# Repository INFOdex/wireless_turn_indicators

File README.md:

# Testing of Wireless Turn Indicators for Automotive Applications
Created as a capstone project for Robert S. and Peter L.

This project was mostly done as a proof-of-concept, but was eventually completed as a capstone project. 

The final copy of the code was stored on the university's private GIT server.

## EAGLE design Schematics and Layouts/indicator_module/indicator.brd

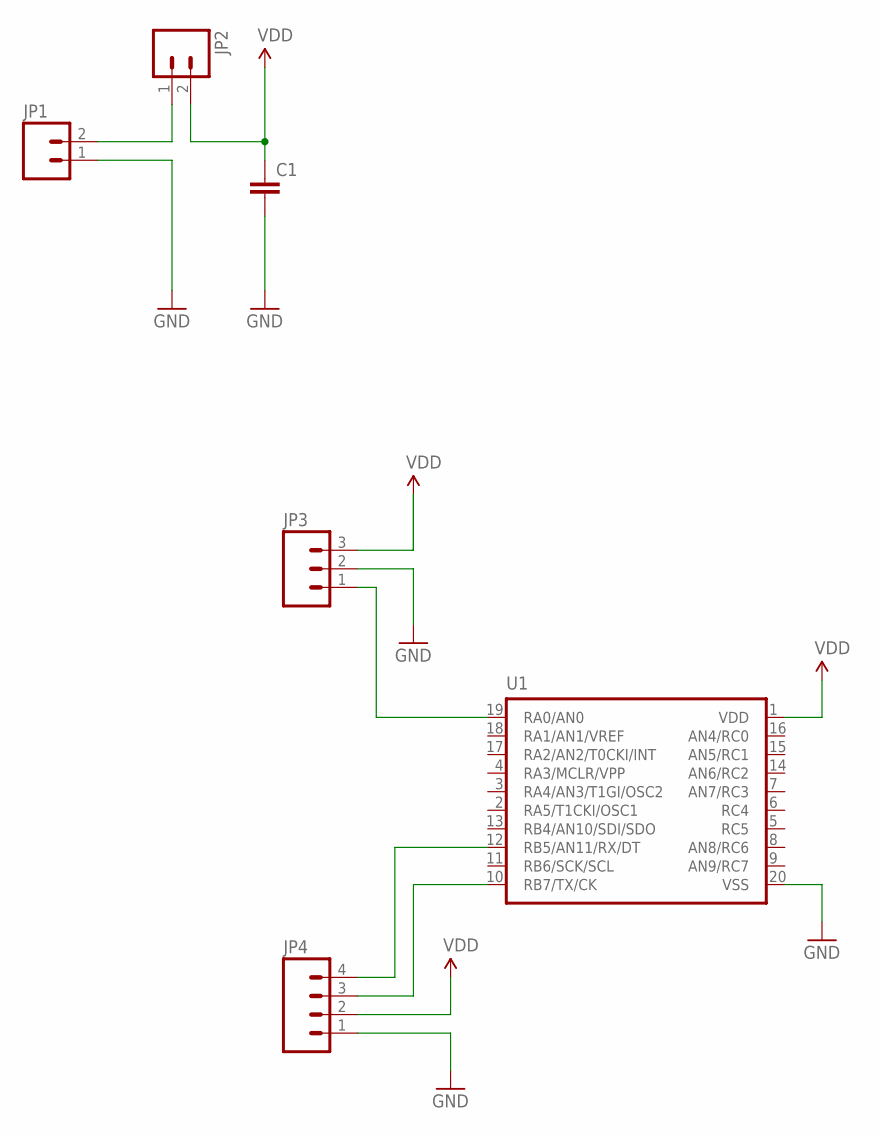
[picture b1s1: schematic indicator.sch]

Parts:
C1: CAPPTH1; CAP-PTH-5MM
JP1, JP2: M02PTH; 1X02
JP3: M03PTH; 1X03
JP4: M04PTH; 1X04
U1: PIC16F6XX; DIL20

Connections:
GND: C1.2, JP1.1, JP3.2, JP4.1, U1.20 (VSS)
unnamed: JP1.2, JP2.1
unnamed: JP3.1, U1.19 (RA0/AN0)
unnamed: JP4.4, U1.12 (RB5/AN11/RX/DT)
unnamed: JP4.3, U1.10 (RB7/TX/CK)
VDD: C1.1, JP2.2, JP3.3, JP4.2, U1.1 (VDD)

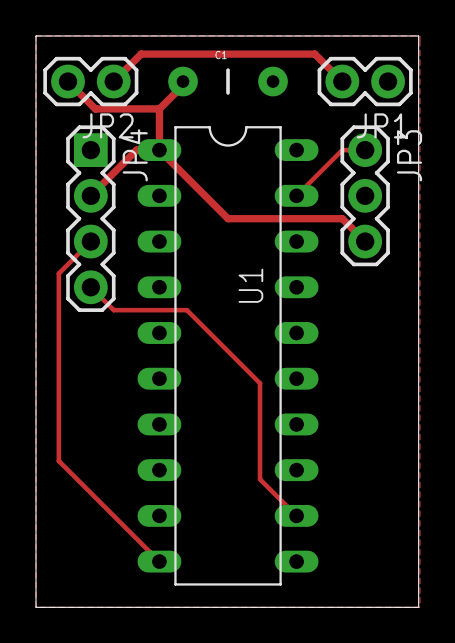
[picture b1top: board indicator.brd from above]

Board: 2 copper layers, 21.3 x 31.7 mm, 6 parts (0 on the bottom side), 6 nets.

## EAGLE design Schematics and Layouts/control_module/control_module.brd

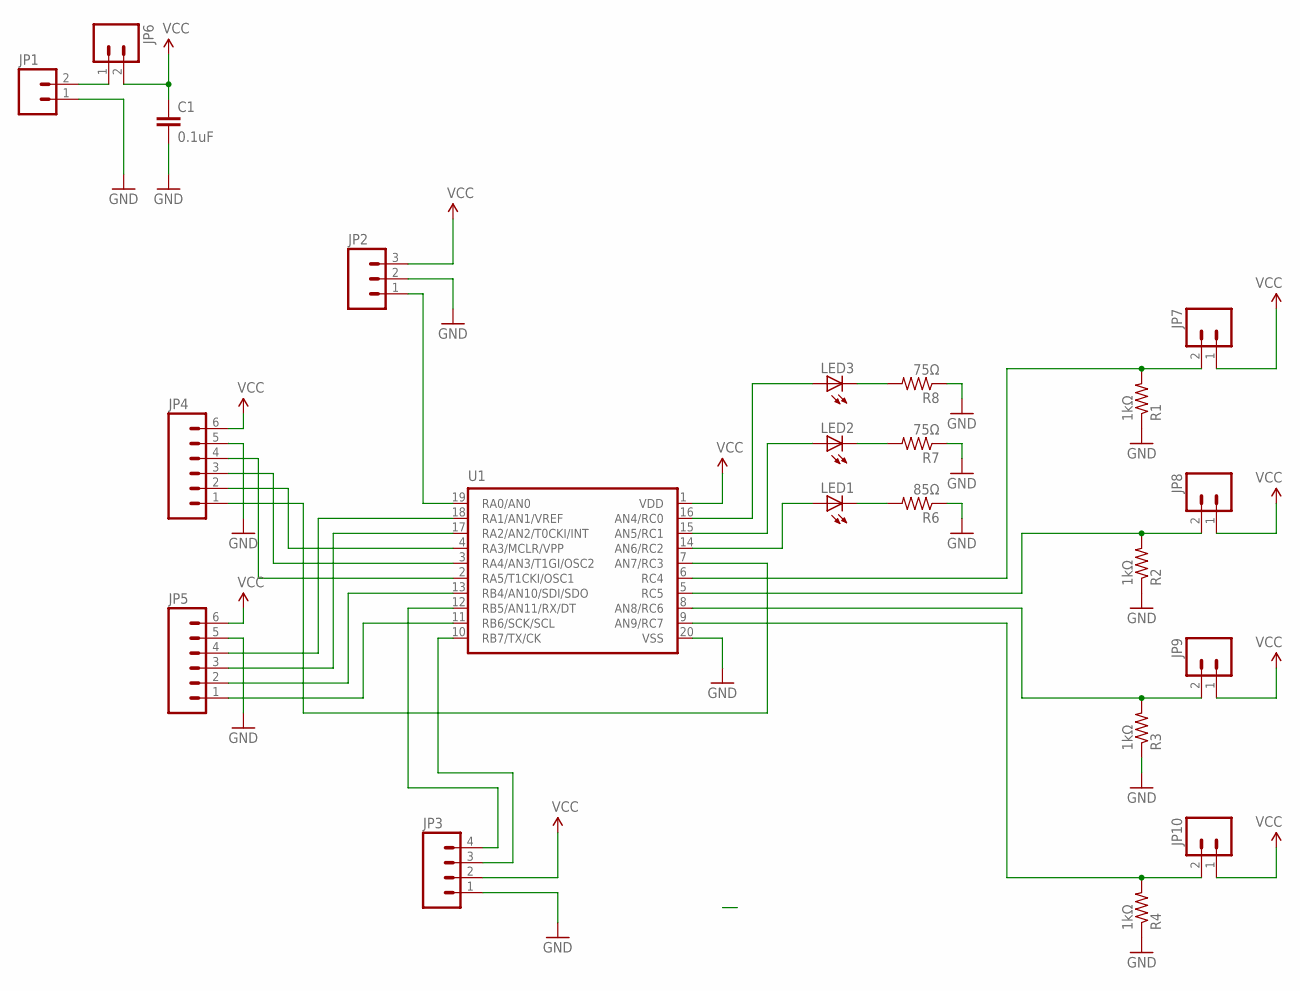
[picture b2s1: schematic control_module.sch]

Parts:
C1: 0.1uF; CAP-PTH-5MM
JP1, JP6, JP7, JP8, JP9, JP10: M02PTH; 1X02
JP2: M03PTH; 1X03
JP3: M04PTH; 1X04
JP4, JP5: M06SILK_FEMALE_PTH; 1X06
LED1, LED2, LED3: LED3MM
R1, R2, R3, R4: 1kΩ; AXIAL-0.4
R6: 85Ω; AXIAL-0.4
R7, R8: 75Ω; AXIAL-0.4
U1: PIC16F6XX; DIL20

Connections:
GND: C1.2, JP1.1, JP2.2, JP3.1, JP4.5, JP5.5, R1.P$1 (1), R2.P$1 (1), R3.P$1 (1), R4.P$1 (1), R6.P$1 (1), R7.P$1 (1), R8.P$1 (1), U1.20 (VSS)
unnamed: JP8.2, R2.P$2 (2), U1.5 (RC5)
unnamed: JP9.2, R3.P$2 (2), U1.8 (AN8/RC6)
unnamed: JP3.4, U1.12 (RB5/AN11/RX/DT)
unnamed: JP10.2, R4.P$2 (2), U1.9 (AN9/RC7)
unnamed: JP2.1, U1.19 (RA0/AN0)
unnamed: LED3.A, U1.16 (AN4/RC0)
unnamed: LED1.K (C), R6.P$2 (2)
unnamed: LED2.A, U1.15 (AN5/RC1)
unnamed: LED2.K (C), R7.P$2 (2)
unnamed: LED1.A, U1.14 (AN6/RC2)
unnamed: LED3.K (C), R8.P$2 (2)
unnamed: JP3.3, U1.10 (RB7/TX/CK)
unnamed: JP4.1, U1.7 (AN7/RC3)
unnamed: JP4.2, U1.4 (RA3/MCLR/VPP)
unnamed: JP4.3, U1.3 (RA4/AN3/T1GI/OSC2)
unnamed: JP4.4, U1.2 (RA5/T1CKI/OSC1)
unnamed: JP5.4, U1.18 (RA1/AN1/VREF)
unnamed: JP5.3, U1.17 (RA2/AN2/T0CKI/INT)
unnamed: JP5.2, U1.13 (RB4/AN10/SDI/SDO)
unnamed: JP1.2, JP6.1
unnamed: JP7.2, R1.P$2 (2), U1.6 (RC4)
unnamed: JP5.1, U1.11 (RB6/SCK/SCL)
VCC: C1.1, JP2.3, JP3.2, JP4.6, JP5.6, JP6.2, JP7.1, JP8.1, JP9.1, JP10.1, U1.1 (VDD)

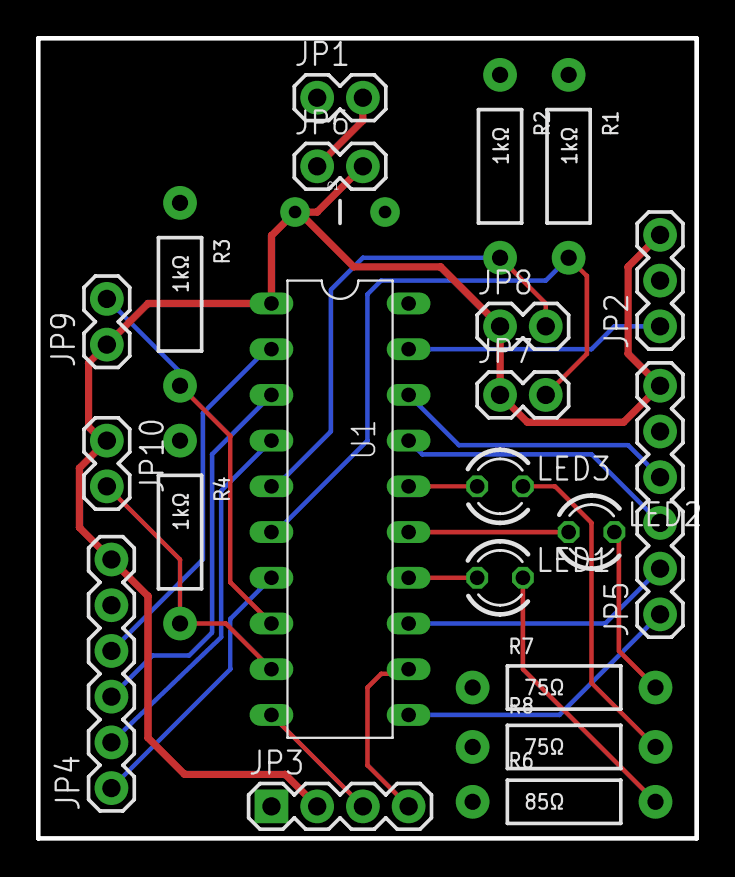
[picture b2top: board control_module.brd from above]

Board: 2 copper layers, 36.6 x 44.5 mm, 22 parts (0 on the bottom side), 24 nets.

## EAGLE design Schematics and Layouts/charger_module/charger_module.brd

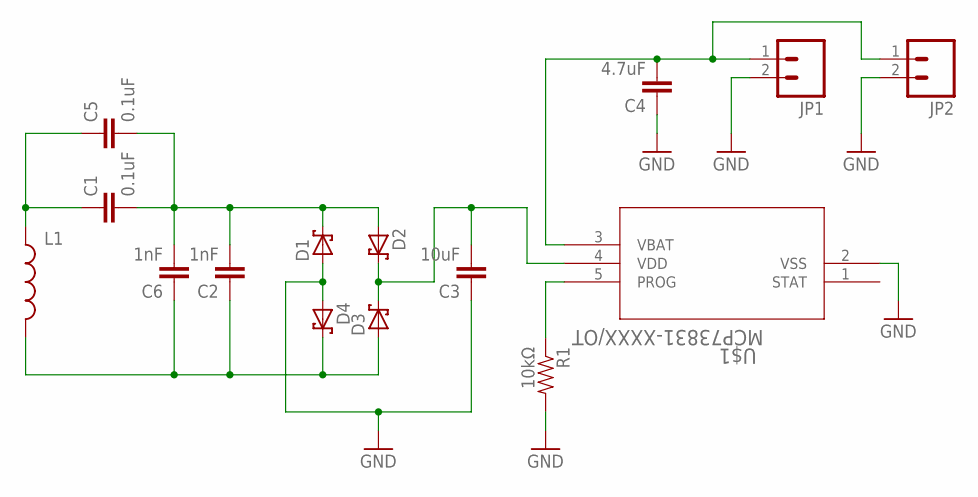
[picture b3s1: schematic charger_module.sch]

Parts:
C1, C5: 0.1uF; CAP-PTH-5MM
C2, C6: 1nF; CAP-PTH-5MM
C3: 10uF; CAP-PTH-5MM
C4: 4.7uF; CAP-PTH-5MM
D1, D2, D3, D4: SCHOTTKY-DIODECB417-15; CB417-15
JP1, JP2: M02PTH; 1X02
L1: INDUCTORAXIAL-0.6; AXIAL-0.6
R1: 10kΩ; AXIAL-0.3
U$1: MCP73831-XXXX/OT; SOT-23-5_MC

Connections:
GND: C3.1, C4.1, D1.A, D4.A, JP1.2, JP2.2, R1.P$2 (2), U$1.2 (VSS)
unnamed: C1.1, C5.1, L1.P$1 (1)
unnamed: C1.2, C2.2, C5.2, C6.2, D1.C, D2.A
unnamed: C3.2, D2.C, D3.C, U$1.4 (VDD)
unnamed: C4.2, JP1.1, JP2.1, U$1.3 (VBAT)
unnamed: C2.1, C6.1, D3.A, D4.C, L1.P$2 (2)
unnamed: R1.P$1 (1), U$1.5 (PROG)

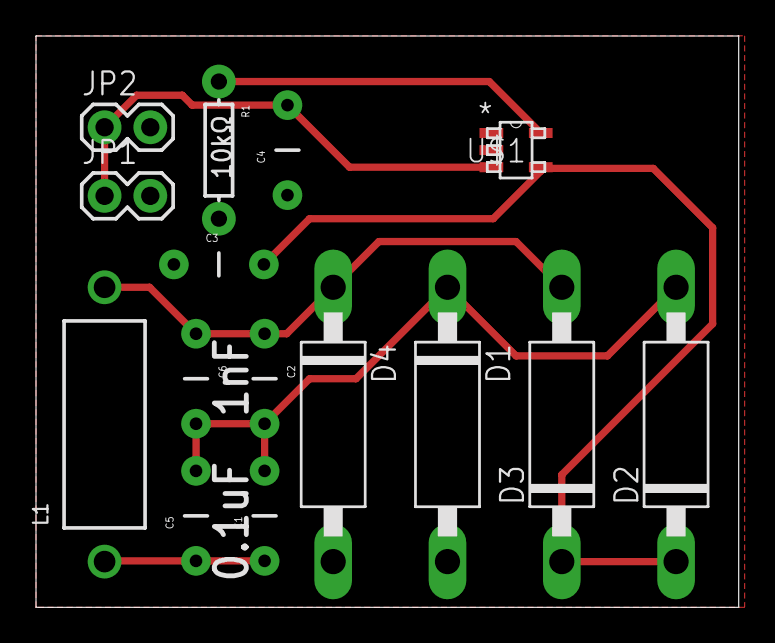
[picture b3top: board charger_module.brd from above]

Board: 2 copper layers, 39.0 x 31.7 mm, 15 parts (0 on the bottom side), 7 nets.

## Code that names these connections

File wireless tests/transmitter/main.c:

#include "uart.h"
#include <pic.h>
#include <htc.h>
#define _LEGACY_HEADERS

// CONFIG
#pragma config FOSC = INTRCIO   // Oscillator Selection bits (INTOSCIO oscillator: I/O function on RA4/OSC2/CLKOUT pin, I/O function on RA5/OSC1/CLKIN)
#pragma config WDTE = OFF       // Watchdog Timer Enable bit (WDT disabled and can be enabled by SWDTEN bit of the WDTCON register)
#pragma config PWRTE = OFF      // Power-up Timer Enable bit (PWRT disabled)
#pragma config MCLRE = OFF      // MCLR Pin Function Select bit (MCLR pin function is digital input, MCLR internally tied to VDD)
#pragma config CP = OFF         // Code Protection bit (Program memory code protection is disabled)
#pragma config CPD = OFF        // Data Code Protection bit (Data memory code protection is disabled)
#pragma config BOREN = OFF      // Brown-out Reset Selection bits (BOR disabled)
#pragma config IESO = OFF       // Internal External Switchover bit (Internal External Switchover mode is disabled)
#pragma config FCMEN = OFF      // Fail-Safe Clock Monitor Enabled bit (Fail-Safe Clock Monitor is disabled)


volatile char count = 0;	//counter to keep track of time in interrupt
volatile int state = 0;     //binary, digital state machine for reset
volatile char buff = 0;		//buffer to be sent
volatile char workaround;   //used to send X (all cancel) via interrupt
volatile char r_blink = 0;	//boolean to denote state of right indicator
volatile char l_blink = 0;	//boolean to denote state of left indicator
volatile char h_blink = 0;	//boolean to denote state of hazard mode
volatile char error_chk = 0; //buffer with error checking result

/*------LEGEND------*/
//X is for all cancel

//R is for right blink
//L is for left blink
//H is for hazard mode
/*------------------*/


void init(void);	//initialization function prototype

void interrupt ISR(void){	//interrupt routine for dash indicator blinking
    //for(int i = 0; i<10000; i++);
    if(RA5 && RABIF){
        count = PORTA;              //read from portA to clear interrupt
        RABIF = 0;                  //clear the flag
        if(l_blink || r_blink || h_blink){
            workaround = 1;                 //for use outside interrupt
        }
        l_blink = 0;        //left off
        r_blink = 0;        //right off
        h_blink = 0;        //hazard mode off
        PORTC = 0;
    }
}

int main(void) {
	RABIF = 0;         //turn off button interrupt flag for good measure
    init();			
	for(int i = 0; i<25000; i++);	//delay used to make sure that UART is set up
	RABIF = 0;          //turn it off again, because it is finicky

	while (1) {
		while((PORTC && 0xF0) == 0);	//check PORTC for button push, hang here if not pushed
		/*TURN LEFT*/	
            while(!l_blink && RC5) {		//RC5 (Left) is pushed & not blinking
				while(RC5);			//debounce
				buff = 76;			//L
				RC1 = 1;            //turn light on to show visual feedback
				UART_sendch(buff);  //send signal to XBee
				l_blink = 1;		//change state to BLINK
            /*----error checking begins below----*/
                for(int i = 0;!RCIF;i++){       //getting response from indicator
                    for(int i = 0; i<10; i++);  //this delay was calibrated via trial and error
                    if(i>10000){                //don't wait here forever (timeout)
                        RC2 = 1;                //ERROR!
                        break;
                    }
                }
                while(RCIF){
                    error_chk = RCREG;          //read the register message until empty
                }
                if(error_chk != 83){ //make sure not garbage
                    RC2 =1;                 //else: ERROR!
                    error_chk = 0;  //reset error-checking buffer after ERROR
                }
                error_chk = 0;      //reset error-checking buffer after success
            /*---error checking completed----*/
                while(l_blink){
                    RC1 = !RC1;     //toggle LED state
                    for(int i = 0; i<27000; i++);   //delay
                }
				
			}
		/*TURN RIGHT*/
			while(!r_blink && RC4) {		//RC4 (Right) is pushed & not blinking
				while(RC4);			//debounce
				buff = 82;			//R
				RC0 = 1;            //turn on LED for visual feedback
				UART_sendch(buff);  //send data to XBee
				r_blink = 1;		//change state to BLINK
                
                for(int i = 0;!RCIF;i++){       //getting response from indicator
                    for(int i = 0; i<10; i++);  //this delay was calibrated via trial and error
                    if(i>10000){                //don't wait here forever (timeout)
                        RC2 = 1;                //ERROR!
                        break;          
                    }
                }
                while(RCIF){
                    error_chk = RCREG;          //read the register message until empty
                }
                if(error_chk != 83){ //make sure not garbage
                    RC2 =1;                 //else: ERROR!
                    error_chk = 0;  //reset error-checking variable after ERROR!
                }
                error_chk = 0;      //reset error-checking variable after success
                
                while(r_blink){
                    RC0 = !RC0;     //toggle LED state
                    for(int i = 0; i<27000; i++);   //delay
                }
			}
		/*HAZARD MODE*/	
			while(!h_blink && RC7) {			//RC7 (Hazard) is pushed
				while(RC7);			//debounce
				buff = 72;			//H
				UART_sendch(buff);  //send data to XBee
				RC0 = 1;			//turn on both dash indicators
				RC1 = 0;            //asynchronously...
				h_blink = 1;		//change state to blink for both indicators
				r_blink = 1;
				l_blink = 1;
                while(h_blink){
                    RC0 = !RC0; //toggle both
                    RC1 = !RC1; //LED states
                    for(int i = 0; i<27000; i++);
                }
			}
        
        if(workaround){     //send all cancel if interrupt sets "workaround" to 1
            buff = 88;          //X
            UART_sendch(buff);  //send data to XBee
            workaround = 0;     //reset workaround        
        }
	}
	return 0;

}


void init(void) {

	//set internal oscillator to 4 MHz (default)
	OSCCON|=0b00111000;

	//set pin RA0 to output
	TRISA=0x3F;

	//set pin RB0 to output
	TRISB=0x00;

	//set pin RC0 to output
	TRISC=0xF0;

	//Initialize PORTS A,B and C
	PORTA=0;
	PORTB=0;
	PORTC=0;

	//configure the device to run as a digital input 
	ANSEL=0;
	ANSELH=0;
	
	//disable comparators
	//CM1CON0 = 0;        //Initialize comp 1 off 
    //CM2CON0 = 0;        //Initialize comp 2 off 

	//Configure Interrupt On Change for RA5
	INTCON = 0x00; 
    IOCA5 = 1;          //Enabled RA5 Interrupt-On-Change 
    RABIF = 0;          //Enabled Interrupt-On-Change Interupt
    RABIE = 1;
    RABIF = 0;
	//INTCON = 0b00001000;
	GIE = 1;		//enable Global interrupts
	
	//ADC_init();
	UART_init();

	
//	RB4=0;
//	RB6=0;
//	delayms(50);
//	RB4=1;
//	RB6=1;
//	delayms(50);
	//RB4=0;
	//RB6=0;
}

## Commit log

2015-07-21 Blinks LED
    (readme included for more detail)
2015-07-22 Start of wireless module testing
    Work in progress... transmitter/receiver still unable to communicate.
    Poor documentation for modules chosen. System works with Xbees, but not
    cheaper modules.
2015-07-23 Transmitter and Receiver Proof of concept updates
    added extra LED for confirmation of button press, and got receiver to
    work properly.
2015-09-30 Transmitter Modification
    Closer to demo version of the code. This is able to blink two different
    lights wirelessly and (mostly) seamlessly.
2015-11-09 Qualifiers (revision 1)
    Schematics, PCB layouts, and a demo version of the code have been
    created/committed.
2015-11-09 Testing the Timer0 interrupt
    Possibly a flawed idea. Made new branch for testing.
2015-11-09 Button interrupts test
    Currently can't leave the ISR, or ISR is continually entered.
2015-11-10 Interrupt on button press (final)
    After hours of chasing my own tail, the interrupt acts as intended. The
    module is closer to final copy than ever before
2015-11-17 Qualifiers Week (final edit)
    Everything works as intended. An indication of error on the transmitter
    module is implemented and is triggered by error on the indicator module.
2015-12-15 Design Review (final FINAL edit)
    Changed when the error is reported (before blinking feedback) and
    changed the error handling to be more robust.
2015-12-15 Added files
    Libraries that I authored to communicate with the XBee via UART.
2015-12-15 Added (one more) library
    Timing library that I modified, but did not author. Obtained from
    MicroChip.
2016-06-06 Updated the readme
    brief clarifications
2016-06-06 Updated the readme
    same as before

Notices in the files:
parts and their libraries:
SparkFun-Passives: Licensing: Creative Commons ShareAlike 4.0 International - https://creativecommons.org/licenses/by-sa/4.0
